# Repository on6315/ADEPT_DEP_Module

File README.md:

# ADEPT_DEP_Module
Adaptable Dielectrophoresis Embedded Platform Tool (ADEPT) 
PCB Hardware design files and corresponding software codes for manufacturing and operating ADEPT for single cell manipulation.

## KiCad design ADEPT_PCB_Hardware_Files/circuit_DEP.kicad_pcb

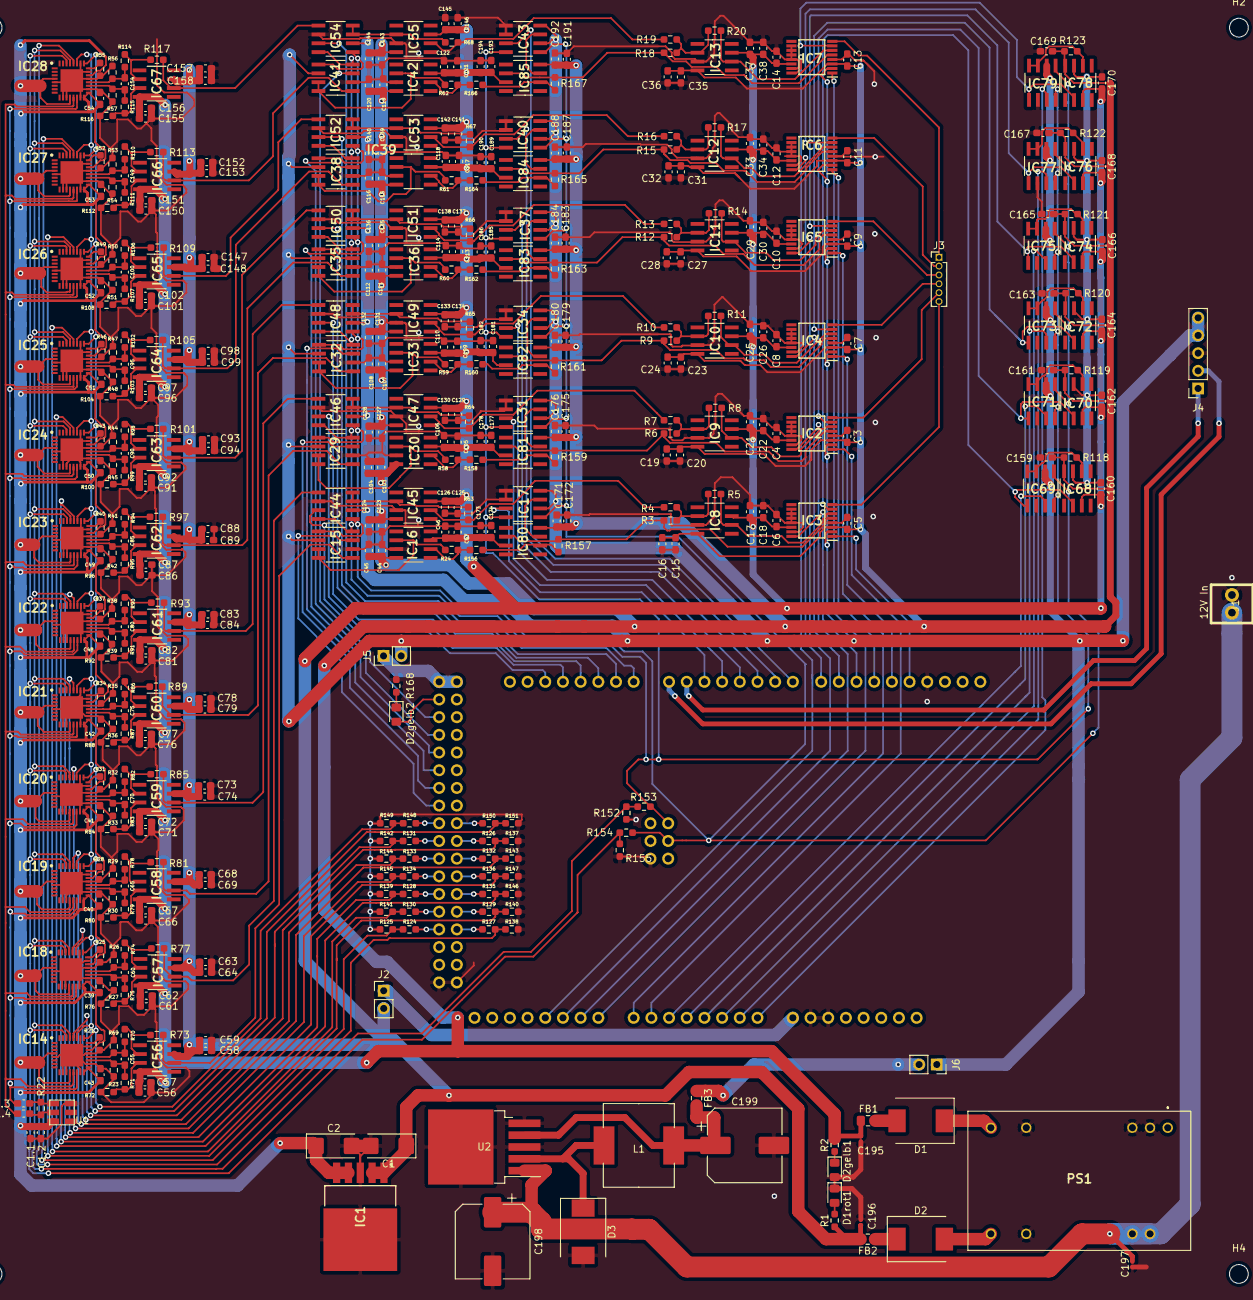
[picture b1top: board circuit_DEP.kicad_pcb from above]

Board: 2 copper layers, 480 parts (1 on the bottom side), 237 nets.

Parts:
C1, C2: 10uF; CP_EIA-6032-28_Kemet-C_Pad2.25x2.35mm_HandSolder
C1.1: 1uF; C_0603_1608Metric_Pad1.08x0.95mm_HandSolder
C1.2, C1.3, C1.4, C39, C40, C41, C42, C43, C48, C49, C50, C51, C52, C53, C54: 0.1uF; C_0603_1608Metric_Pad1.08x0.95mm_HandSolder
C3, C4, C5, C6, C7, C8, C9, C10, C11, C12, C13, C14: 10nF; C_0603_1608Metric_Pad1.08x0.95mm_HandSolder
C15, C17, C19, C21, C23, C25, C27, C29, C31, C33, C35, C37, C44, C46, C56, C58, C61, C63, C66, C68, C71, C73, C76, C78, C81, C83, C86, C88, C91, C93, C96, C98, C101, C103, C105, C107, C109, C111, C113, C115, C117, C119, C121, C123, C125, C127, C129, C131, C133, C135, C137, C139, C141, C143, C145, C147, C150, C152, C155, C157, C171, C173, C175, C177, C179, C181, C183, C185, C187, C189, C191, C193: 10uF; C_0603_1608Metric_Pad1.08x0.95mm_HandSolder
C16, C18, C20, C22, C24, C26, C28, C30, C32, C34, C36, C38, C45, C47, C57, C59, C62, C64, C67, C69, C72, C74, C77, C79, C82, C84, C87, C89, C92, C94, C97, C99, C102, C104, C106, C108, C110, C112, C114, C116, C118, C120, C122, C124, C126, C128, C130, C132, C134, C136, C138, C140, C142, C144, C146, C148, C151, C153, C156, C158, C172, C174, C176, C178, C180, C182, C184, C186, C188, C190, C192, C194: 0.01uF; C_0603_1608Metric_Pad1.08x0.95mm_HandSolder
C55, C60, C65, C70, C75, C80, C85, C90, C95, C100, C149, C154: 0.1n; C_0603_1608Metric_Pad1.08x0.95mm_HandSolder
C159, C161, C163, C165, C167, C169: 0.1u; C_0603_1608Metric_Pad1.08x0.95mm_HandSolder
C160, C162, C164, C166, C168, C170: C; C_0603_1608Metric_Pad1.08x0.95mm_HandSolder
C195, C196: 10uF; C_0201_0603Metric_Pad0.64x0.40mm_HandSolder
C197: 0.1uF; C_0201_0603Metric_Pad0.64x0.40mm_HandSolder
C198: 680uF; CP_Elec_10x10.5
C199: 220uF; CP_Elec_10x10.5
D1, D2, D3: D; D_SMC
D1rot1, D2gelb1, D2gelb2: 1.8; D_0805_2012Metric_Pad1.15x1.40mm_HandSolder
FB1, FB2, FB3: Ferrite_Bead; C_0805_2012Metric_Pad1.18x1.45mm_HandSolder
H1, H2, H3, H4: MountingHole; MountingHole_2.7mm
IC1: LT1764AEQ-1.8#PBF; TO170P1394X457-6N
IC2, IC3, IC4, IC5, IC6, IC7: MAX14753EUE+; SOP65P640X110-16N
IC8, IC9, IC10, IC11, IC12, IC13, IC16, IC30, IC33, IC36, IC39, IC42, IC45, IC47, IC49, IC51, IC53, IC55, IC56, IC57, IC58, IC59, IC60, IC61, IC62, IC63, IC64, IC65, IC66, IC67, IC80, IC81, IC82, IC83, IC84, IC85: AD825ARZ; SOIC127P600X175-8N
IC14, IC18, IC19, IC20, IC21, IC22, IC23, IC24, IC25, IC26, IC27, IC28: AD9913BCPZ; QFN50P500X500X100-33N
IC15, IC17, IC29, IC31, IC32, IC34, IC35, IC37, IC38, IC40, IC41, IC43, IC44, IC46, IC48, IC50, IC52, IC54, IC69, IC71, IC73, IC75, IC77, IC79: AD8400ARZ10; SOIC127P600X175-8N
IC68, IC70, IC72, IC74, IC76, IC78: OPA277UA; SOIC127P600X175-8N
J1: Conn_01x02_Male; con_supply
J2, J5: Conn_01x02_Male; PinHeader_1x02_P2.54mm_Vertical
J3: Conn_01x06_Male; PinHeader_1x06_P1.27mm_Vertical
J4: Conn_01x05_Female; PinSocket_1x05_P2.54mm_Vertical
J6: Conn_01x02_Male; PinSocket_1x02_P2.54mm_Vertical
L1: 33u; inductor_gen
PS1: NCS12S1205D; NCS12D1212C
R1, R2: 6.8k; R_0603_1608Metric_Pad0.98x0.95mm_HandSolder
R3, R4, R5, R6, R7, R8, R9, R10, R11, R12, R13, R14, R15, R16, R17, R18, R19, R20, R24, R58, R59, R60, R61, R62, R63, R64, R65, R66, R67, R68, R118, R119, R120, R121, R122, R123, R124, R125, R126, R127, R128, R129, R130, R131, R132, R133, R134, R135, R136, R137, R138, R139, R140, R141, R142, R143, R144, R145, R146, R147, R148, R149, R150, R151, R152, R153, R154, R155, R156, R157, R158, R159, R160, R161, R162, R163, R164, R165, R166, R167: R; R_0603_1608Metric_Pad0.98x0.95mm_HandSolder
R21, R25, R28, R31, R34, R37, R40, R43, R46, R49, R52, R55: 4.64k; R_0603_1608Metric_Pad0.98x0.95mm_HandSolder
R22: 100; R_0603_1608Metric_Pad0.98x0.95mm_HandSolder
R23, R26, R27, R29, R30, R32, R33, R35, R36, R38, R39, R41, R42, R44, R45, R47, R48, R50, R51, R53, R54, R56, R57, R69: 50; R_0603_1608Metric_Pad0.98x0.95mm_HandSolder
R70, R71, R74, R75, R78, R79, R82, R83, R86, R87, R90, R91, R94, R95, R98, R99, R102, R103, R106, R107, R110, R111, R114, R115: 500; R_0603_1608Metric_Pad0.98x0.95mm_HandSolder
R72, R73, R76, R77, R80, R81, R84, R85, R88, R89, R92, R93, R96, R97, R100, R101, R104, R105, R108, R109, R112, R113, R116, R117: 1000; R_0603_1608Metric_Pad0.98x0.95mm_HandSolder
R168: 1.6k; R_0603_1608Metric_Pad0.98x0.95mm_HandSolder
U1: 511JBA250M000BAG
U2: LM2596S-5; TO-263-5_TabPin3
XA1: Arduino_Mega2560_Shield

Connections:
1.8MOSI: IC14.29, IC18.29, IC19.29, IC20.29, IC21.29, IC22.29, IC23.29, IC24.29, IC25.29, IC26.29, IC27.29, IC28.29, R152.1, R153.1
1.8SCLK: IC14.30, IC18.30, IC19.30, IC20.30, IC21.30, IC22.30, IC23.30, IC24.30, IC25.30, IC26.30, IC27.30, IC28.30, R154.1, R155.1
+1V8: C1.1.2, C1.2.2, C2.1, C39.1, C40.1, C41.1, C42.1, C43.1, C48.1, C49.1, C50.1, C51.1, C52.1, C53.1, C54.1, IC1.4, IC1.5, IC14.4, IC14.12, IC14.16, IC14.17, IC14.22, IC18.4, IC18.12, IC18.16, IC18.17, IC18.22, IC19.4, IC19.12, IC19.16, IC19.17, IC19.22, IC20.4, IC20.12, IC20.16, IC20.17, IC20.22, IC21.4, IC21.12, IC21.16, IC21.17, IC21.22, IC22.4, IC22.12, IC22.16, IC22.17, IC22.22, IC23.4, IC23.12, IC23.16, IC23.17, IC23.22, IC24.4, IC24.12, IC24.16, IC24.17, IC24.22, IC25.4, IC25.12, IC25.16, IC25.17, IC25.22, IC26.4, IC26.12, IC26.16, IC26.17, IC26.22, IC27.4, IC27.12, IC27.16, IC27.17, IC27.22, IC28.4, IC28.12, IC28.16, IC28.17, IC28.22, U1.4
+5V: IC2.2, IC3.2, IC4.2, IC5.2, IC6.2, IC7.2, IC15.6, IC17.6, IC17.8, IC29.6, IC31.6, IC31.8, IC32.6, IC34.6, IC34.8, IC35.6, IC37.6, IC37.8, IC38.6, IC40.6, IC40.8, IC41.6, IC43.6, IC43.8, IC44.6, IC46.6, IC48.6, IC50.6, IC52.6, IC54.6, IC69.6, IC71.6, IC73.6, IC75.6, IC77.6, IC79.6, J4.4, J4.5, J5.2, J6.1
+12V: C1.1, C4.1, C6.1, C8.1, C10.1, C12.1, C14.1, C17.1, C18.1, C21.1, C22.1, C25.1, C26.1, C29.1, C30.1, C33.1, C34.1, C37.1, C38.1, C46.1, C47.1, C58.1, C59.1, C63.1, C64.1, C68.1, C69.1, C73.1, C74.1, C78.1, C79.1, C83.1, C84.1, C88.1, C89.1, C93.1, C94.1, C98.1, C99.1, C105.1, C106.1, C109.1, C110.1, C113.1, C114.1, C117.1, C118.1, C121.1, C122.1, C125.1, C126.1, C129.1, C130.1, C133.1, C134.1, C137.1, C138.1, C141.1, C142.1, C145.1, C146.1, C147.1, C148.1, C152.1, C153.1, C157.1, C158.1, C160.2, C162.2, C164.2, C166.2, C168.2, C170.2, C173.1, C174.1, C177.1, C178.1, C181.1, C182.1, C185.1, C186.1, C189.1, C190.1, C193.1, C194.1, C196.1, FB2.2, IC1.1, IC1.2, IC2.14, IC3.14, IC4.14, IC5.14, IC6.14, IC7.14, IC8.7, IC9.7, IC10.7, IC11.7, IC12.7, IC13.7, IC16.7, IC30.7, IC33.7, IC36.7, IC39.7, IC42.7, IC45.7, IC47.7, IC49.7, IC51.7, IC53.7, IC55.7, IC56.7, IC57.7, IC58.7, IC59.7, IC60.7, IC61.7, IC62.7, IC63.7, IC64.7, IC65.7, IC66.7, IC67.7, IC68.7, IC70.7, IC72.7, IC74.7, IC76.7, IC78.7, IC80.7, IC81.7, IC82.7, IC83.7, IC84.7, IC85.7, J2.2, R1.1
-12V: C3.1, C5.1, C7.1, C9.1, C11.1, C13.1, C15.1, C16.1, C19.1, C20.1, C23.1, C24.1, C27.1, C28.1, C31.1, C32.1, C35.1, C36.1, C44.1, C45.1, C56.1, C57.1, C61.1, C62.1, C66.1, C67.1, C71.1, C72.1, C76.1, C77.1, C81.1, C82.1, C86.1, C87.1, C91.1, C92.1, C96.1, C97.1, C101.1, C102.1, C103.1, C104.1, C107.1, C108.1, C111.1, C112.1, C115.1, C116.1, C119.1, C120.1, C123.1, C124.1, C127.1, C128.1, C131.1, C132.1, C135.1, C136.1, C139.1, C140.1, C143.1, C144.1, C150.1, C151.1, C155.1, C156.1, C159.1, C161.1, C163.1, C165.1, C167.1, C169.1, C171.1, C172.1, C175.1, C176.1, C179.1, C180.1, C183.1, C184.1, C187.1, C188.1, C191.1, C192.1, C195.1, FB1.2, IC2.3, IC3.3, IC4.3, IC5.3, IC6.3, IC7.3, IC8.4, IC9.4, IC10.4, IC11.4, IC12.4, IC13.4, IC16.4, IC30.4, IC33.4, IC36.4, IC39.4, IC42.4, IC45.4, IC47.4, IC49.4, IC51.4, IC53.4, IC55.4, IC56.4, IC57.4, IC58.4, IC59.4, IC60.4, IC61.4, IC62.4, IC63.4, IC64.4, IC65.4, IC66.4, IC67.4, IC68.4, IC70.4, IC72.4, IC74.4, IC76.4, IC78.4, IC80.4, IC81.4, IC82.4, IC83.4, IC84.4, IC85.4, R2.2, R118.1, R119.1, R120.1, R121.1, R122.1, R123.1
/Sheet60A37CB5/AM1.1/in1: IC15.1, IC56.6, R73.1
/Sheet60A37CB5/AM1.2/in1: IC44.1, IC57.6, R77.1
/Sheet60A37CB5/AM1.2/out: IC45.6, R4.2, R63.1
/Sheet60A37CB5/AM2.1/in1: IC29.1, IC58.6, R81.1
/Sheet60A37CB5/AM2.2/in1: IC46.1, IC59.6, R85.1
/Sheet60A37CB5/AM2.2/out: IC47.6, R7.2, R64.1
/Sheet60A37CB5/AM3.1/in1: IC32.1, IC60.6, R89.1
/Sheet60A37CB5/AM3.2/in1: IC48.1, IC61.6, R93.1
/Sheet60A37CB5/AM3.2/out: IC49.6, R10.2, R65.1
/Sheet60A37CB5/AM4.1/in1: IC35.1, IC62.6, R97.1
/Sheet60A37CB5/AM4.2/in1: IC50.1, IC63.6, R101.1
/Sheet60A37CB5/AM4.2/out: IC51.6, R13.2, R66.1
/Sheet60A37CB5/AM5.1/in1: IC38.1, IC64.6, R105.1
/Sheet60A37CB5/AM5.2/in1: IC52.1, IC65.6, R109.1
/Sheet60A37CB5/AM5.2/out: IC53.6, R16.2, R67.1
/Sheet60A37CB5/AM6.1/in1: IC41.1, IC66.6, R113.1
/Sheet60A37CB5/AM6.2/in1: IC54.1, IC67.6, R117.1
/Sheet60A37CB5/AM6.2/out: IC55.6, R19.2, R68.1
/Sheet60A37CB5/MUX1/S1: IC3.5, IC80.6, R3.2, R157.1
/Sheet60A37CB5/MUX1/S2: IC3.7, IC68.6, IC69.1
/Sheet60A37CB5/MUX1/out: IC3.8, J3.6
/Sheet60A37CB5/MUX2/S1: IC2.5, IC81.6, R6.2, R159.1
/Sheet60A37CB5/MUX2/S2: IC2.7, IC70.6, IC71.1
/Sheet60A37CB5/MUX2/out: IC2.8, J3.5
/Sheet60A37CB5/MUX3/S1: IC4.5, IC82.6, R9.2, R161.1
/Sheet60A37CB5/MUX3/S2: IC4.7, IC72.6, IC73.1
/Sheet60A37CB5/MUX3/out: IC4.8, J3.4
/Sheet60A37CB5/MUX4/S1: IC5.5, IC83.6, R12.2, R163.1
/Sheet60A37CB5/MUX4/S2: IC5.7, IC74.6, IC75.1
/Sheet60A37CB5/MUX4/out: IC5.8, J3.3
/Sheet60A37CB5/MUX5/S1: IC6.5, IC84.6, R15.2, R165.1
/Sheet60A37CB5/MUX5/S2: IC6.7, IC76.6, IC77.1
/Sheet60A37CB5/MUX5/out: IC6.8, J3.2
/Sheet60A37CB5/MUX6/S1: IC7.5, IC85.6, R18.2, R167.1
/Sheet60A37CB5/MUX6/S2: IC7.7, IC78.6, IC79.1
/Sheet60A37CB5/MUX6/out: IC7.8, J3.1
/Sheet60A37CB5/SG1.1/Iout: C55.1, IC14.20, R69.1, R70.2
/Sheet60A37CB5/SG1.2/Iout: C60.1, IC18.20, R26.1, R74.2
/Sheet60A37CB5/SG2.1/Iout: C65.1, IC19.20, R29.1, R78.2
/Sheet60A37CB5/SG2.2/Iout: C70.1, IC20.20, R32.1, R82.2
/Sheet60A37CB5/SG3.1/Iout: C75.1, IC21.20, R35.1, R86.2
/Sheet60A37CB5/SG3.2/Iout: C80.1, IC22.20, R38.1, R90.2
/Sheet60A37CB5/SG4.1/Iout: C85.1, IC23.20, R41.1, R94.2
/Sheet60A37CB5/SG4.2/Iout: C90.1, IC24.20, R44.1, R98.2
/Sheet60A37CB5/SG5.1/Iout: C95.1, IC25.20, R47.1, R102.2
/Sheet60A37CB5/SG5.2/Iout: C100.1, IC26.20, R50.1, R106.2
/Sheet60A37CB5/SG6.1/Iout: C149.1, IC27.20, R53.1, R110.2
/Sheet60A37CB5/SG6.2/Iout: C154.1, IC28.20, R56.1, R114.2
/Sheet60A37CB5/SUM1/out: IC3.6, IC8.6, R5.1
/Sheet60A37CB5/SUM2/out: IC2.6, IC9.6, R8.1
/Sheet60A37CB5/SUM3/out: IC4.6, IC10.6, R11.1
/Sheet60A37CB5/SUM4/out: IC5.6, IC11.6, R14.1
/Sheet60A37CB5/SUM5/out: IC6.6, IC12.6, R17.1
/Sheet60A37CB5/SUM6/out: IC7.6, IC13.6, R20.1
/Sheet60A37CB5/preamp1/in2: C55.2, IC14.19, R23.2, R71.2
/Sheet60A37CB5/preamp2/in2: C60.2, IC18.19, R27.2, R75.2
/Sheet60A37CB5/preamp3/in2: C65.2, IC19.19, R30.2, R79.2
/Sheet60A37CB5/preamp4/in2: C70.2, IC20.19, R33.2, R83.2
/Sheet60A37CB5/preamp5/in2: C75.2, IC21.19, R36.2, R87.2
/Sheet60A37CB5/preamp6/in2: C80.2, IC22.19, R39.2, R91.2
/Sheet60A37CB5/preamp7/in2: C85.2, IC23.19, R42.2, R95.2
/Sheet60A37CB5/preamp8/in2: C90.2, IC24.19, R45.2, R99.2
/Sheet60A37CB5/preamp9/in2: C95.2, IC25.19, R48.2, R103.2
/Sheet60A37CB5/preamp10/in2: C100.2, IC26.19, R51.2, R107.2
/Sheet60A37CB5/preamp11/in2: C149.2, IC27.19, R54.2, R111.2
/Sheet60A37CB5/preamp12/in2: C154.2, IC28.19, R57.2, R115.2
CLK+: C1.4.1, IC14.13, IC18.13, IC19.13, IC20.13, IC21.13, IC22.13, IC23.13, IC24.13, IC25.13, IC26.13, IC27.13, IC28.13
CLK-: C1.3.1, IC14.14, IC18.14, IC19.14, IC20.14, IC21.14, IC22.14, IC23.14, IC24.14, IC25.14, IC26.14, IC27.14, IC28.14
GND: C1.2, C1.1.1, C1.2.1, C2.2, C3.2, C4.2, C5.2, C6.2, C7.2, C8.2, C9.2, C10.2, C11.2, C12.2, C13.2, C14.2, C15.2, C16.2, C17.2, C18.2, C19.2, C20.2, C21.2, C22.2, C23.2, C24.2, C25.2, C26.2, C27.2, C28.2, C29.2, C30.2, C31.2, C32.2, C33.2, C34.2, C35.2, C36.2, C37.2, C38.2, C39.2, C40.2, C41.2, C42.2, C43.2, C44.2, C45.2, C46.2, C47.2, C48.2, C49.2, C50.2, C51.2, C52.2, C53.2, C54.2, C56.2, C57.2, C58.2, C59.2, C61.2, C62.2, C63.2, C64.2, C66.2, C67.2, C68.2, C69.2, C71.2, C72.2, C73.2, C74.2, C76.2, C77.2, C78.2, C79.2, C81.2, C82.2, C83.2, C84.2, C86.2, C87.2, C88.2, C89.2, C91.2, C92.2, C93.2, C94.2, C96.2, C97.2, C98.2, C99.2, C101.2, C102.2, C103.2, C104.2, C105.2, C106.2, C107.2, C108.2, C109.2, C110.2, C111.2, C112.2, C113.2, C114.2, C115.2, C116.2, C117.2, C118.2, C119.2, C120.2, C121.2, C122.2, C123.2, C124.2, C125.2, C126.2, C127.2, C128.2, C129.2, C130.2, C131.2, C132.2, C133.2, C134.2, C135.2, C136.2, C137.2, C138.2, C139.2, C140.2, C141.2, C142.2, C143.2, C144.2, C145.2, C146.2, C147.2, C148.2, C150.2, C151.2, C152.2, C153.2, C155.2, C156.2, C157.2, C158.2, C159.2, C160.1, C161.2, C162.1, C163.2, C164.1, C165.2, C166.1, C167.2, C168.1, C169.2, C170.1, C171.2, C172.2, C173.2, C174.2, C175.2, C176.2, C177.2, C178.2, C179.2, C180.2, C181.2, C182.2, C183.2, C184.2, C185.2, C186.2, C187.2, C188.2, C189.2, C190.2, C191.2, C192.2, C193.2, C194.2, C195.2, C196.2, C197.1, C198.2, C199.2, D1rot1.1, D2gelb1.2, D3.2, IC1.3, IC1.6, IC2.4, IC2.10, IC2.11, IC2.12, IC2.13, IC2.15, IC3.4, IC3.10, IC3.11, IC3.12, IC3.13, IC3.15, IC4.4, IC4.10, IC4.11, IC4.12, IC4.13, IC4.15, IC5.4, IC5.10, IC5.11, IC5.12, IC5.13, IC5.15, IC6.4, IC6.10, IC6.11, IC6.12, IC6.13, IC6.15, IC7.4, IC7.10, IC7.11, IC7.12, IC7.13, IC7.15, IC8.3, IC9.3, IC10.3, IC11.3, IC12.3, IC13.3, IC14.5, IC14.10, IC14.11, IC14.15, IC14.18, IC14.21, IC14.23, IC14.26, IC14.33, IC15.2, IC16.3, IC17.1, IC17.2, IC18.5, IC18.10, IC18.11, IC18.15, IC18.18, IC18.21, IC18.23, IC18.26, IC18.33, IC19.5, IC19.10, IC19.11, IC19.15, IC19.18, IC19.21, IC19.23, IC19.26, IC19.33, IC20.5, IC20.10, IC20.11, IC20.15, IC20.18, IC20.21, IC20.23, IC20.26, IC20.33, IC21.5, IC21.10, IC21.11, IC21.15, IC21.18, IC21.21, IC21.23, IC21.26, IC21.33, IC22.5, IC22.10, IC22.11, IC22.15, IC22.18, IC22.21, IC22.23, IC22.26, IC22.33, IC23.5, IC23.10, IC23.11, IC23.15, IC23.18, IC23.21, IC23.23, IC23.26, IC23.33, IC24.5, IC24.10, IC24.11, IC24.15, IC24.18, IC24.21, IC24.23, IC24.26, IC24.33, IC25.5, IC25.10, IC25.11, IC25.15, IC25.18, IC25.21, IC25.23, IC25.26, IC25.33, IC26.5, IC26.10, IC26.11, IC26.15, IC26.18, IC26.21, IC26.23, IC26.26, IC26.33, IC27.5, IC27.10, IC27.11, IC27.15, IC27.18, IC27.21, IC27.23, IC27.26, IC27.33, IC28.5, IC28.10, IC28.11, IC28.15, IC28.18, IC28.21, IC28.23, IC28.26, IC28.33, IC29.2, IC30.3, IC31.1, IC31.2, IC32.2, IC33.3, IC34.1, IC34.2, IC35.2, IC36.3, IC37.1, IC37.2, IC38.2, IC39.3, IC40.1, IC40.2, IC41.2, IC42.3, IC43.1, IC43.2, IC44.2, IC45.3, IC46.2, IC47.3, IC48.2, IC49.3, IC50.2, IC51.3, IC52.2, IC53.3, IC54.2, IC55.3, IC68.3, IC69.2, IC70.3, IC71.2, IC72.3, IC73.2, IC74.3, IC75.2, IC76.3, IC77.2, IC78.3, IC79.2, J1.2, J4.3, PS1.2, PS1.3, PS1.9, PS1.16, R21.1, R23.1, R25.1, R26.2, R27.1, R28.1, R29.2, R30.1, R31.1, R32.2, R33.1, R34.1, R35.2, R36.1, R37.1, R38.2, R39.1, R40.1, R41.2, R42.1, R43.1, R44.2, R45.1, R46.1, R47.2, R48.1, R49.1, R50.2, R51.1, R52.1, R53.2, R54.1, R55.1, R56.2, R57.1, R69.2, R72.2, R76.2, R80.2, R84.2, R88.2, R92.2, R96.2, R100.2, R104.2, R108.2, R112.2, R116.2, R125.1, R137.1, R138.1, R139.1, R140.1, R141.1, R142.1, R143.1, R144.1, R145.1, R146.1, R147.1, R149.1, R151.1, R152.2, R155.2, R168.1, U1.3, U2.3, U2.5, XA1.GND1, XA1.GND2, XA1.GND3, XA1.GND4, XA1.GND5, XA1.GND6
Global_IO_update: IC14.27, IC18.27, IC19.27, IC20.27, IC21.27, IC22.27, IC23.27, IC24.27, IC25.27, IC26.27, IC27.27, IC28.27, R150.1, R151.2
MOSI: IC15.4, IC17.4, IC29.4, IC31.4, IC32.4, IC34.4, IC35.4, IC37.4, IC38.4, IC40.4, IC41.4, IC43.4, IC44.4, IC46.4, IC48.4, IC50.4, IC52.4, IC54.4, IC69.4, IC71.4, IC73.4, IC75.4, IC77.4, IC79.4, R153.2, XA1.MISO
MUX1.1: IC3.1, XA1.D13
MUX1.2: IC3.16, XA1.D10
MUX2.1: IC2.1, XA1.A6
MUX2.2: IC2.16, XA1.A9
MUX3.1: IC4.1, XA1.D12
MUX3.2: IC4.16, XA1.D9
MUX4.1: IC5.1, XA1.A7
MUX4.2: IC5.16, XA1.A10
MUX5.1: IC6.1, XA1.D11
MUX5.2: IC6.16, XA1.D8
MUX6.1: IC7.1, XA1.A8
MUX6.2: IC7.16, XA1.A11
Master_reset: IC14.25, IC18.25, IC19.25, IC20.25, IC21.25, IC22.25, IC23.25, IC24.25, IC25.25, IC26.25, IC27.25, IC28.25, R148.1, R149.2
unnamed: C1.3.2, R22.1, U1.6
unnamed: C1.4.2, R22.2, U1.5
unnamed: C197.2, C198.1, J1.1, PS1.22, PS1.23, U2.1
unnamed: C199.1, FB3.2, L1.2, U2.4
unnamed: D1.1, PS1.11
unnamed: D1.2, FB1.1
unnamed: D1rot1.2, R1.2
unnamed: D2.1, FB2.1
unnamed: D2.2, PS1.14
unnamed: D2gelb1.1, R2.1
unnamed: D2gelb2.1, R168.2
unnamed: D2gelb2.2, XA1.D23
unnamed: D3.1, L1.1, U2.2
unnamed: FB3.1, J6.2
unnamed: IC8.2, R3.1, R4.1, R5.2
unnamed: IC9.2, R6.1, R7.1, R8.2
unnamed: IC10.2, R9.1, R10.1, R11.2
unnamed: IC11.2, R12.1, R13.1, R14.2
unnamed: IC12.2, R15.1, R16.1, R17.2
unnamed: IC13.2, R18.1, R19.1, R20.2
unnamed: IC14.24, R21.2
unnamed: IC15.7, IC15.8, IC16.2, R24.2
unnamed: IC16.6, R24.1, R156.2
unnamed: IC17.7, IC80.3
unnamed: IC18.24, R25.2
unnamed: IC19.24, R28.2
unnamed: IC20.24, R31.2
unnamed: IC21.24, R34.2
unnamed: IC22.24, R37.2
unnamed: IC23.24, R40.2
unnamed: IC24.24, R43.2
unnamed: IC25.24, R46.2
unnamed: IC26.24, R49.2
unnamed: IC27.24, R52.2
unnamed: IC28.24, R55.2
unnamed: IC29.7, IC29.8, IC30.2, R58.2
unnamed: IC30.6, R58.1, R158.2
unnamed: IC31.7, IC81.3
unnamed: IC32.7, IC32.8, IC33.2, R59.2
unnamed: IC33.6, R59.1, R160.2
unnamed: IC34.7, IC82.3
unnamed: IC35.7, IC35.8, IC36.2, R60.2
unnamed: IC36.6, R60.1, R162.2
unnamed: IC37.7, IC83.3
unnamed: IC38.7, IC38.8, IC39.2, R61.2
unnamed: IC39.6, R61.1, R164.2
unnamed: IC40.7, IC84.3
unnamed: IC41.7, IC41.8, IC42.2, R62.2
unnamed: IC42.6, R62.1, R166.2
unnamed: IC43.7, IC85.3
unnamed: IC44.7, IC44.8, IC45.2, R63.2
unnamed: IC46.7, IC46.8, IC47.2, R64.2
unnamed: IC48.7, IC48.8, IC49.2, R65.2
unnamed: IC50.7, IC50.8, IC51.2, R66.2
unnamed: IC52.7, IC52.8, IC53.2, R67.2
unnamed: IC54.7, IC54.8, IC55.2, R68.2
unnamed: IC56.2, R70.1, R73.2
unnamed: IC56.3, R71.1, R72.1
unnamed: IC57.2, R74.1, R77.2
unnamed: IC57.3, R75.1, R76.1
unnamed: IC58.2, R78.1, R81.2
unnamed: IC58.3, R79.1, R80.1
unnamed: IC59.2, R82.1, R85.2
unnamed: IC59.3, R83.1, R84.1
unnamed: IC60.2, R86.1, R89.2
unnamed: IC60.3, R87.1, R88.1
unnamed: IC61.2, R90.1, R93.2
unnamed: IC61.3, R91.1, R92.1
unnamed: IC62.2, R94.1, R97.2
unnamed: IC62.3, R95.1, R96.1
unnamed: IC63.2, R98.1, R101.2
unnamed: IC63.3, R99.1, R100.1
unnamed: IC64.2, R102.1, R105.2
unnamed: IC64.3, R103.1, R104.1
unnamed: IC65.2, R106.1, R109.2
unnamed: IC65.3, R107.1, R108.1
unnamed: IC66.2, R110.1, R113.2
unnamed: IC66.3, R111.1, R112.1
unnamed: IC67.2, R114.1, R117.2
unnamed: IC67.3, R115.1, R116.1
unnamed: IC68.2, IC69.7, IC69.8, R118.2
unnamed: IC70.2, IC71.7, IC71.8, R119.2
unnamed: IC72.2, IC73.7, IC73.8, R120.2
unnamed: IC74.2, IC75.7, IC75.8, R121.2
unnamed: IC76.2, IC77.7, IC77.8, R122.2
unnamed: IC78.2, IC79.7, IC79.8, R123.2
unnamed: IC80.2, R156.1, R157.2
unnamed: IC81.2, R158.1, R159.2
unnamed: IC82.2, R160.1, R161.2
unnamed: IC83.2, R162.1, R163.2
unnamed: IC84.2, R164.1, R165.2
unnamed: IC85.2, R166.1, R167.2
unnamed: J2.1, XA1.VIN
unnamed: J4.1, XA1.D1
unnamed: J4.2, XA1.D0
unnamed: J5.1, XA1.5V3, XA1.5V4
unnamed: R124.2, XA1.D49
unnamed: R126.2, XA1.D38
unnamed: R127.2, XA1.D48
unnamed: R128.2, XA1.D45
unnamed: R129.2, XA1.D46
unnamed: R130.2, XA1.D47
unnamed: R131.2, XA1.D39
unnamed: R132.2, XA1.D40
unnamed: R133.2, XA1.D41
unnamed: R134.2, XA1.D43
unnamed: R135.2, XA1.D44
unnamed: R136.2, XA1.D42
unnamed: R148.2, XA1.D37
unnamed: R150.2, XA1.D36
R1.1: IC15.3, XA1.D35
R1.2: IC17.3, XA1.D2
R1.3: IC44.3, XA1.D19
R1DC: IC69.3, XA1.A5
R2.1: IC29.3, XA1.D33
R2.2: IC31.3, XA1.D3
R2.3: IC46.3, XA1.D18
R2DC: IC71.3, XA1.A4
R3.1: IC32.3, XA1.D31
R3.2: IC34.3, XA1.D4
R3.3: IC48.3, XA1.D17
R3DC: IC73.3, XA1.A3
R4.1: IC35.3, XA1.D29
R4.2: IC37.3, XA1.D5
R4.3: IC50.3, XA1.D16
R4DC: IC75.3, XA1.A2
R5.1: IC38.3, XA1.D27
R5.2: IC40.3, XA1.D6
R5.3: IC52.3, XA1.D15
R5DC: IC77.3, XA1.A1
R6.1: IC41.3, XA1.D25
R6.2: IC43.3, XA1.D7
R6.3: IC54.3, XA1.D14
R6DC: IC79.3, XA1.A0
SCLK: IC15.5, IC17.5, IC29.5, IC31.5, IC32.5, IC34.5, IC35.5, IC37.5, IC38.5, IC40.5, IC41.5, IC43.5, IC44.5, IC46.5, IC48.5, IC50.5, IC52.5, IC54.5, IC69.5, IC71.5, IC73.5, IC75.5, IC77.5, IC79.5, R154.2, XA1.SCK
SG1.1: IC14.28, R131.1, R142.2
SG1.2: IC18.28, R126.1, R137.2
SG2.1: IC19.28, R133.1, R144.2
SG2.2: IC20.28, R132.1, R143.2
SG3.1: IC21.28, R134.1, R145.2
SG3.2: IC22.28, R136.1, R147.2
SG4.1: IC23.28, R128.1, R139.2
SG4.2: IC24.28, R135.1, R146.2
SG5.1: IC25.28, R130.1, R141.2
SG5.2: IC26.28, R129.1, R140.2
SG6.1: IC27.28, R124.1, R125.2
SG6.2: IC28.28, R127.1, R138.2

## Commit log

2023-02-24 Create empty
